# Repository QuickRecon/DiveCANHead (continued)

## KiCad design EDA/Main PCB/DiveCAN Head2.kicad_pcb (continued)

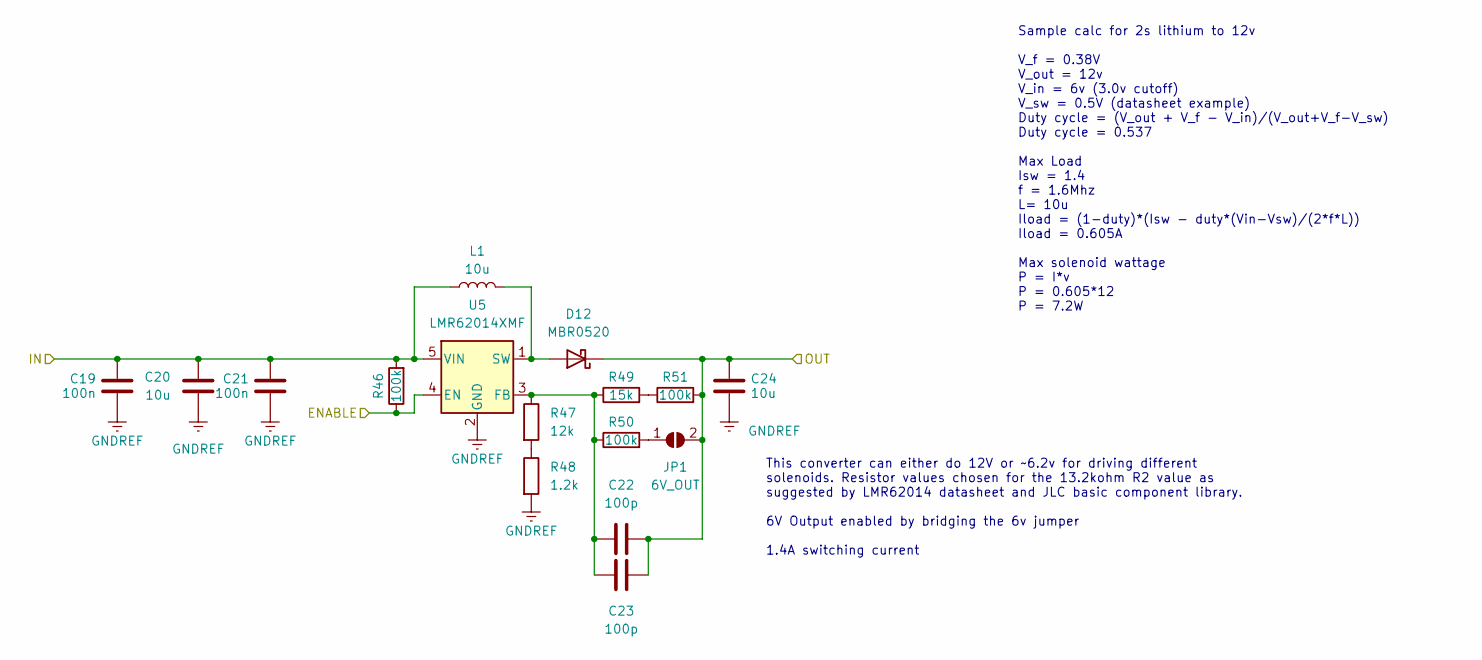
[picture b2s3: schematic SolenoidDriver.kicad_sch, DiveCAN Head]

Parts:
C19, C21: 100n; C_0603_1608Metric; MPN C14663
C20, C24: 10u; C_0603_1608Metric; MPN C96446
C22, C23: 100p; C_0402_1005Metric; MPN C1546
D12: MBR0520; D_SOD-123; MPN C5204745
JP1: 6V_OUT; SolderJumper-2_P1.3mm_Open_TrianglePad1.0x1.5mm
L1: 10u; L_SunItech_SLO0530H; MPN C325966
R46, R50, R51: 100k; R_0402_1005Metric; MPN C25741
R47: 12k; R_0402_1005Metric; MPN C25752
R48: 1.2k; R_0402_1005Metric; MPN C25862
R49: 15k; R_0402_1005Metric; MPN C25756
U5: LMR62014XMF; SOT-23-5; MPN C468235

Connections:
/Power Distribution/SOLENOID_PWR: C19.2, C20.1, C21.2, L1.1, R46.2, U5.5 (VIN); also elsewhere on the board
/SOLENOID: R46.1, U5.4 (EN); also elsewhere on the board
/SOL_OUT: C22.1, C23.1, C24.1, D12.1 (K), JP1.2 (B), R51.2; also elsewhere on the board
GNDREF: C19.1, C20.2, C21.1, C24.2, R48.2, U5.2 (GND); also elsewhere on the board
unnamed: D12.2 (A), L1.2, U5.1 (SW)
unnamed: JP1.1 (A), R50.2
unnamed: R47.2, R48.1
unnamed: R49.2, R51.1
unnamed: C22.2, C23.2, R47.1, R49.1, R50.1, U5.3 (FB)

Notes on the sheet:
Sample calc for 2s lithium to 12v V_f = 0.38V V_out = 12v V_in = 6v (3.0v cutoff) V_sw = 0.5V (datasheet example) Duty cycle = (V_out + V_f - V_in)/(V_out+V_f-V_sw) Duty cycle = 0.537 Max Load Isw = 1.4 f = 1.6Mhz L= 10u Iload = (1-duty)*(Isw - duty*(Vin-Vsw)/(2*f*L)) Iload = 0.605A Max solenoid wa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
This converter can either do 12V or ~6.2v for driving different solenoids. Resistor values chosen for the 13.2kohm R2 value as suggested by LMR62014 datasheet and JLC basic component library. 6V Output enabled by bridging the 6v jumper 1.4A switching current

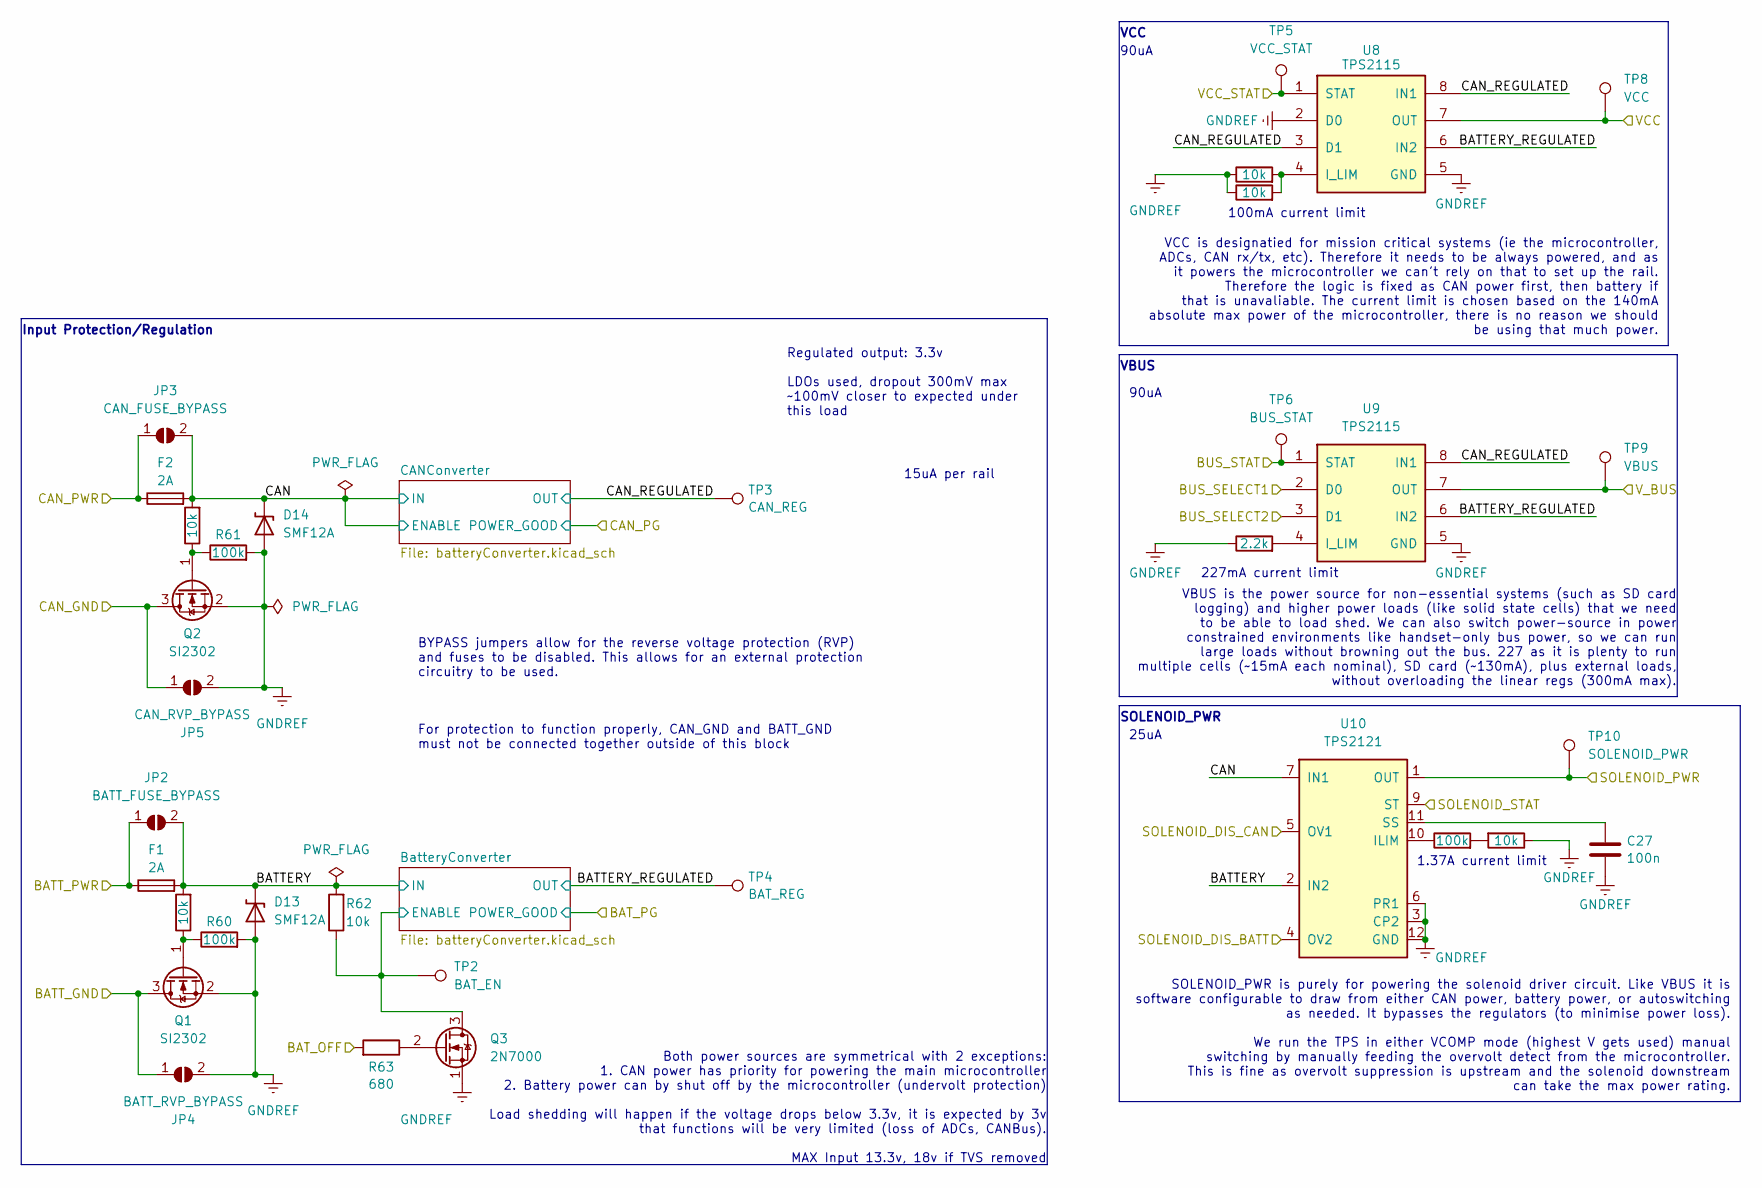
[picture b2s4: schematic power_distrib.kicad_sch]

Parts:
C27: 100n; C_0603_1608Metric; MPN C14663
D13, D14: SMF12A; D_SOD-123F; MPN C178259
F1, F2: 2A; Fuseholder_Littelfuse_Nano2_154x; MPN C108518
JP2: BATT_FUSE_BYPASS; SolderJumper-2_P1.3mm_Open_TrianglePad1.0x1.5mm
JP3: CAN_FUSE_BYPASS; SolderJumper-2_P1.3mm_Open_TrianglePad1.0x1.5mm
JP4: BATT_RVP_BYPASS; SolderJumper-2_P1.3mm_Open_TrianglePad1.0x1.5mm
JP5: CAN_RVP_BYPASS; SolderJumper-2_P1.3mm_Open_TrianglePad1.0x1.5mm
Q1, Q2: SI2302; SOT-23; MPN C181087; JlcRotOffset 180
Q3: 2N7000; SOT-23; MPN C8545; JlcRotOffset 180
R58, R59, R62, R65, R66, R70: 10k; R_0402_1005Metric; MPN C25744
R60, R61, R69: 100k; R_0402_1005Metric; MPN C25741
R63: 680; R_0402_1005Metric; MPN C25130
R67: 2.2k; R_0402_1005Metric; MPN C25879
TP2: BAT_EN; TestPoint_THTPad_D1.0mm_Drill0.5mm
TP3: CAN_REG; TestPoint_THTPad_D1.0mm_Drill0.5mm
TP4: BAT_REG; TestPoint_THTPad_D1.0mm_Drill0.5mm
TP5: VCC_STAT; TestPoint_THTPad_D1.0mm_Drill0.5mm
TP6: BUS_STAT; TestPoint_THTPad_D1.0mm_Drill0.5mm
TP8: VCC; TestPoint_THTPad_D1.0mm_Drill0.5mm
TP9: VBUS; TestPoint_THTPad_D1.0mm_Drill0.5mm
TP10: SOLENOID_PWR; TestPoint_THTPad_D1.0mm_Drill0.5mm
U8, U9: TPS2115; VSON-8_3.3x3.3mm_P0.65mm_NexFET; MPN C140321; JLCPCB Rotation Offset 90
U10: TPS2121; Texas_VQFN-HR-12_2x2.5mm_P0.5mm; JLC Part # C485916

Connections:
/BATTERY: F1.1, JP2.1 (A); also elsewhere on the board
/BATT_OFF: R63.2; also elsewhere on the board
/BUS_SEL1: U9.2 (D0); also elsewhere on the board
/BUS_SEL2: U9.3 (D1); also elsewhere on the board
/BUS_STAT: TP6.1, U9.1 (STAT); also elsewhere on the board
/CAN_GND: JP5.1 (A), Q2.3 (D); also elsewhere on the board
/CAN_PWR: F2.1, JP3.1 (A); also elsewhere on the board
/Power Distribution/BATTERY: D13.1 (A1), F1.2, JP2.2 (B), R58.2, R62.2, U10.2 (IN2); also elsewhere on the board
/Power Distribution/BATTERY_REGULATED: TP4.1, U8.6 (IN2), U9.6 (IN2); also elsewhere on the board
/Power Distribution/BATT_GND: JP4.1 (A), Q1.3 (D); also elsewhere on the board
/Power Distribution/BatteryConverter/ENABLE: Q3.3 (D), R62.1, TP2.1; also elsewhere on the board
/Power Distribution/CAN: D14.1 (A1), F2.2, JP3.2 (B), R59.2, U10.7 (IN1); also elsewhere on the board
/Power Distribution/CAN_REGULATED: TP3.1, U8.3 (D1), U8.8 (IN1), U9.8 (IN1); also elsewhere on the board
/Power Distribution/SOLENOID_PWR: TP10.1, U10.1 (OUT), U10.8 (OUT); also elsewhere on the board
/SOL_DIS_BATT: U10.4 (OV2); also elsewhere on the board
/SOL_DIS_CAN: U10.5 (OV1); also elsewhere on the board
/SOL_STAT: U10.9 (ST); also elsewhere on the board
/VCC_STAT: TP5.1, U8.1 (STAT); also elsewhere on the board
GNDREF: C27.2, D13.2 (A2), D14.2 (A2), JP4.2 (B), JP5.2 (B), Q1.2 (S), Q2.2 (S), Q3.1 (S), R60.2, R61.2, R65.1, R66.1, R67.1, R70.1, U8.2 (D0), U8.5 (GND), U9.5 (GND), U10.3 (CP2), U10.6 (PR1), U10.12 (GND); also elsewhere on the board
unnamed: Q1.1 (G), R58.1, R60.1
unnamed: Q2.1 (G), R59.1, R61.1
unnamed: Q3.2 (G), R63.1
unnamed: R69.2, R70.2
unnamed: R65.2, R66.2, U8.4 (I_LIM)
unnamed: R67.2, U9.4 (I_LIM)
unnamed: R69.1, U10.10 (ILIM)
unnamed: C27.1, U10.11 (SS)
VBUS: TP9.1, U9.7 (OUT); also elsewhere on the board
VCC: TP8.1, U8.7 (OUT); also elsewhere on the board

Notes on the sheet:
Both power sources are symmetrical with 2 exceptions: 1. CAN power has priority for powering the main microcontroller 2. Battery power can by shut off by the microcontroller (undervolt protection) Load shedding will happen if the voltage drops below 3.3v, it is expected by 3v that functions will be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
SOLENOID_PWR
25uA
VBUS is the power source for non-essential systems (such as SD card logging) and higher power loads (like solid state cells) that we need to be able to load shed. We can also switch power-source in power constrained environments like handset-only bus power, so we can run large loads without brownin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
15uA per rail
100mA current limit
90uA
Input Protection/Regulation
227mA current limit
VCC is designatied for mission critical systems (ie the microcontroller, ADCs, CAN rx/tx, etc). Therefore it needs to be always powered, and as it powers the microcontroller we can't rely on that to set up the rail. Therefore the logic is fixed as CAN power first, then battery if that is unavaliabl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
VCC
Regulated output: 3.3v LDOs used, dropout 300mV max ~100mV closer to expected under this load
VBUS
For protection to function properly, CAN_GND and BATT_GND must not be connected together outside of this block
1.37A current limit
BYPASS jumpers allow for the reverse voltage protection (RVP) and fuses to be disabled. This allows for an external protection circuitry to be used.
SOLENOID_PWR is purely for powering the solenoid driver circuit. Like VBUS it is software configurable to draw from either CAN power, battery power, or autoswitching as needed. It bypasses the regulators (to minimise power loss). We run the TPS in either VCOMP mode (highest V gets used) manual swit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

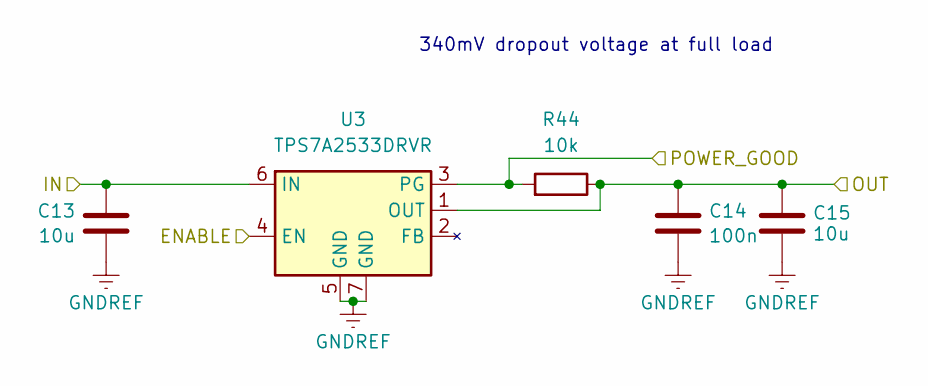
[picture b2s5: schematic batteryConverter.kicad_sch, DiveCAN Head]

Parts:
C13, C15: 10u; C_0603_1608Metric; MPN C96446
C14: 100n; C_0603_1608Metric; MPN C14663
R44: 10k; R_0402_1005Metric; MPN C25744
U3: TPS7A2533DRVR; WSON-6-1EP_2x2mm_P0.65mm_EP1x1.6mm_ThermalVias; MPN C2867820; JlcRotOffset 0

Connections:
/Power Distribution/CAN: C13.1, U3.4 (EN), U3.6 (IN); also elsewhere on the board
/Power Distribution/CAN_PG: R44.2, U3.3 (PG)
/Power Distribution/CAN_REGULATED: C14.1, C15.1, R44.1, U3.1 (OUT); also elsewhere on the board
GNDREF: C13.2, C14.2, C15.2, U3.5 (GND), U3.7 (GND); also elsewhere on the board

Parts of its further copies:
C16, C18: 10u; C_0603_1608Metric; MPN C96446
C17: 100n; C_0603_1608Metric; MPN C14663
R45: 10k; R_0402_1005Metric; MPN C25744
U4: TPS7A2533DRVR; WSON-6-1EP_2x2mm_P0.65mm_EP1x1.6mm_ThermalVias; MPN C2867820; JlcRotOffset 0

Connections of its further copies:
/Power Distribution/BATTERY: C16.1, U4.6 (IN); also elsewhere on the board
/Power Distribution/BATTERY_REGULATED: C17.1, C18.1, R45.1, U4.1 (OUT); also elsewhere on the board
/Power Distribution/BAT_PG: R45.2, U4.3 (PG)
/Power Distribution/BatteryConverter/ENABLE: U4.4 (EN); also elsewhere on the board
GNDREF: C16.2, C17.2, C18.2, U4.5 (GND), U4.7 (GND); also elsewhere on the board

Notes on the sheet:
340mV dropout voltage at full load

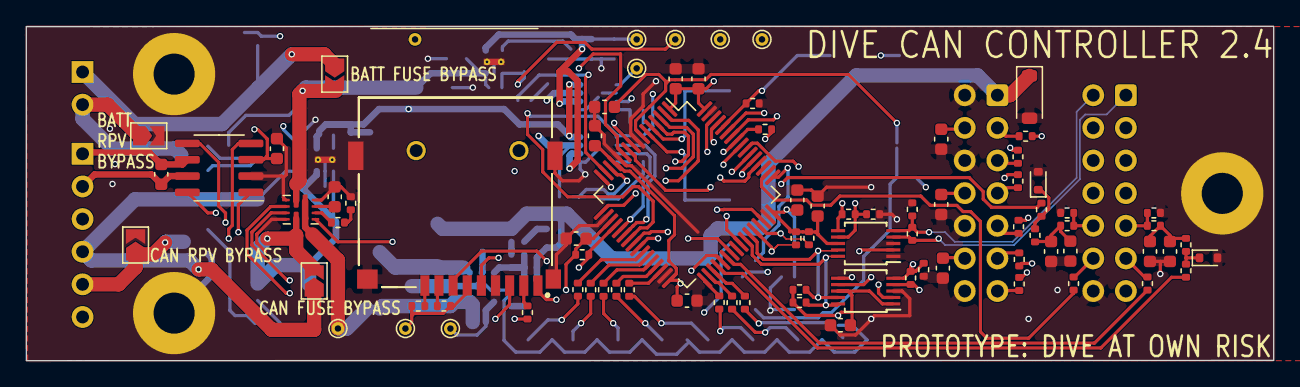
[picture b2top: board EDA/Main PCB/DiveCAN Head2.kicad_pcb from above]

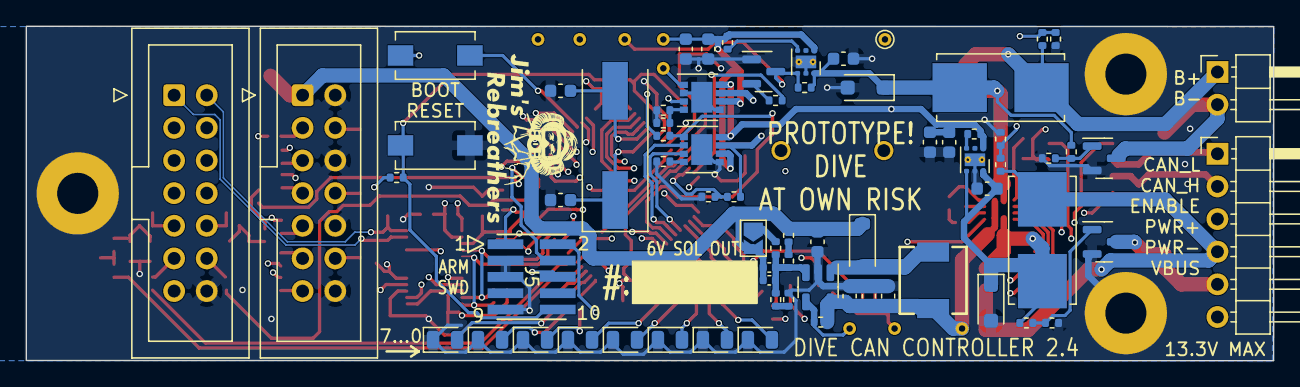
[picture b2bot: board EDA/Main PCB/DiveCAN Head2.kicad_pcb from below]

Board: 4 copper layers, 97.1 x 26.0 mm, 156 parts (71 on the bottom side), 114 nets.

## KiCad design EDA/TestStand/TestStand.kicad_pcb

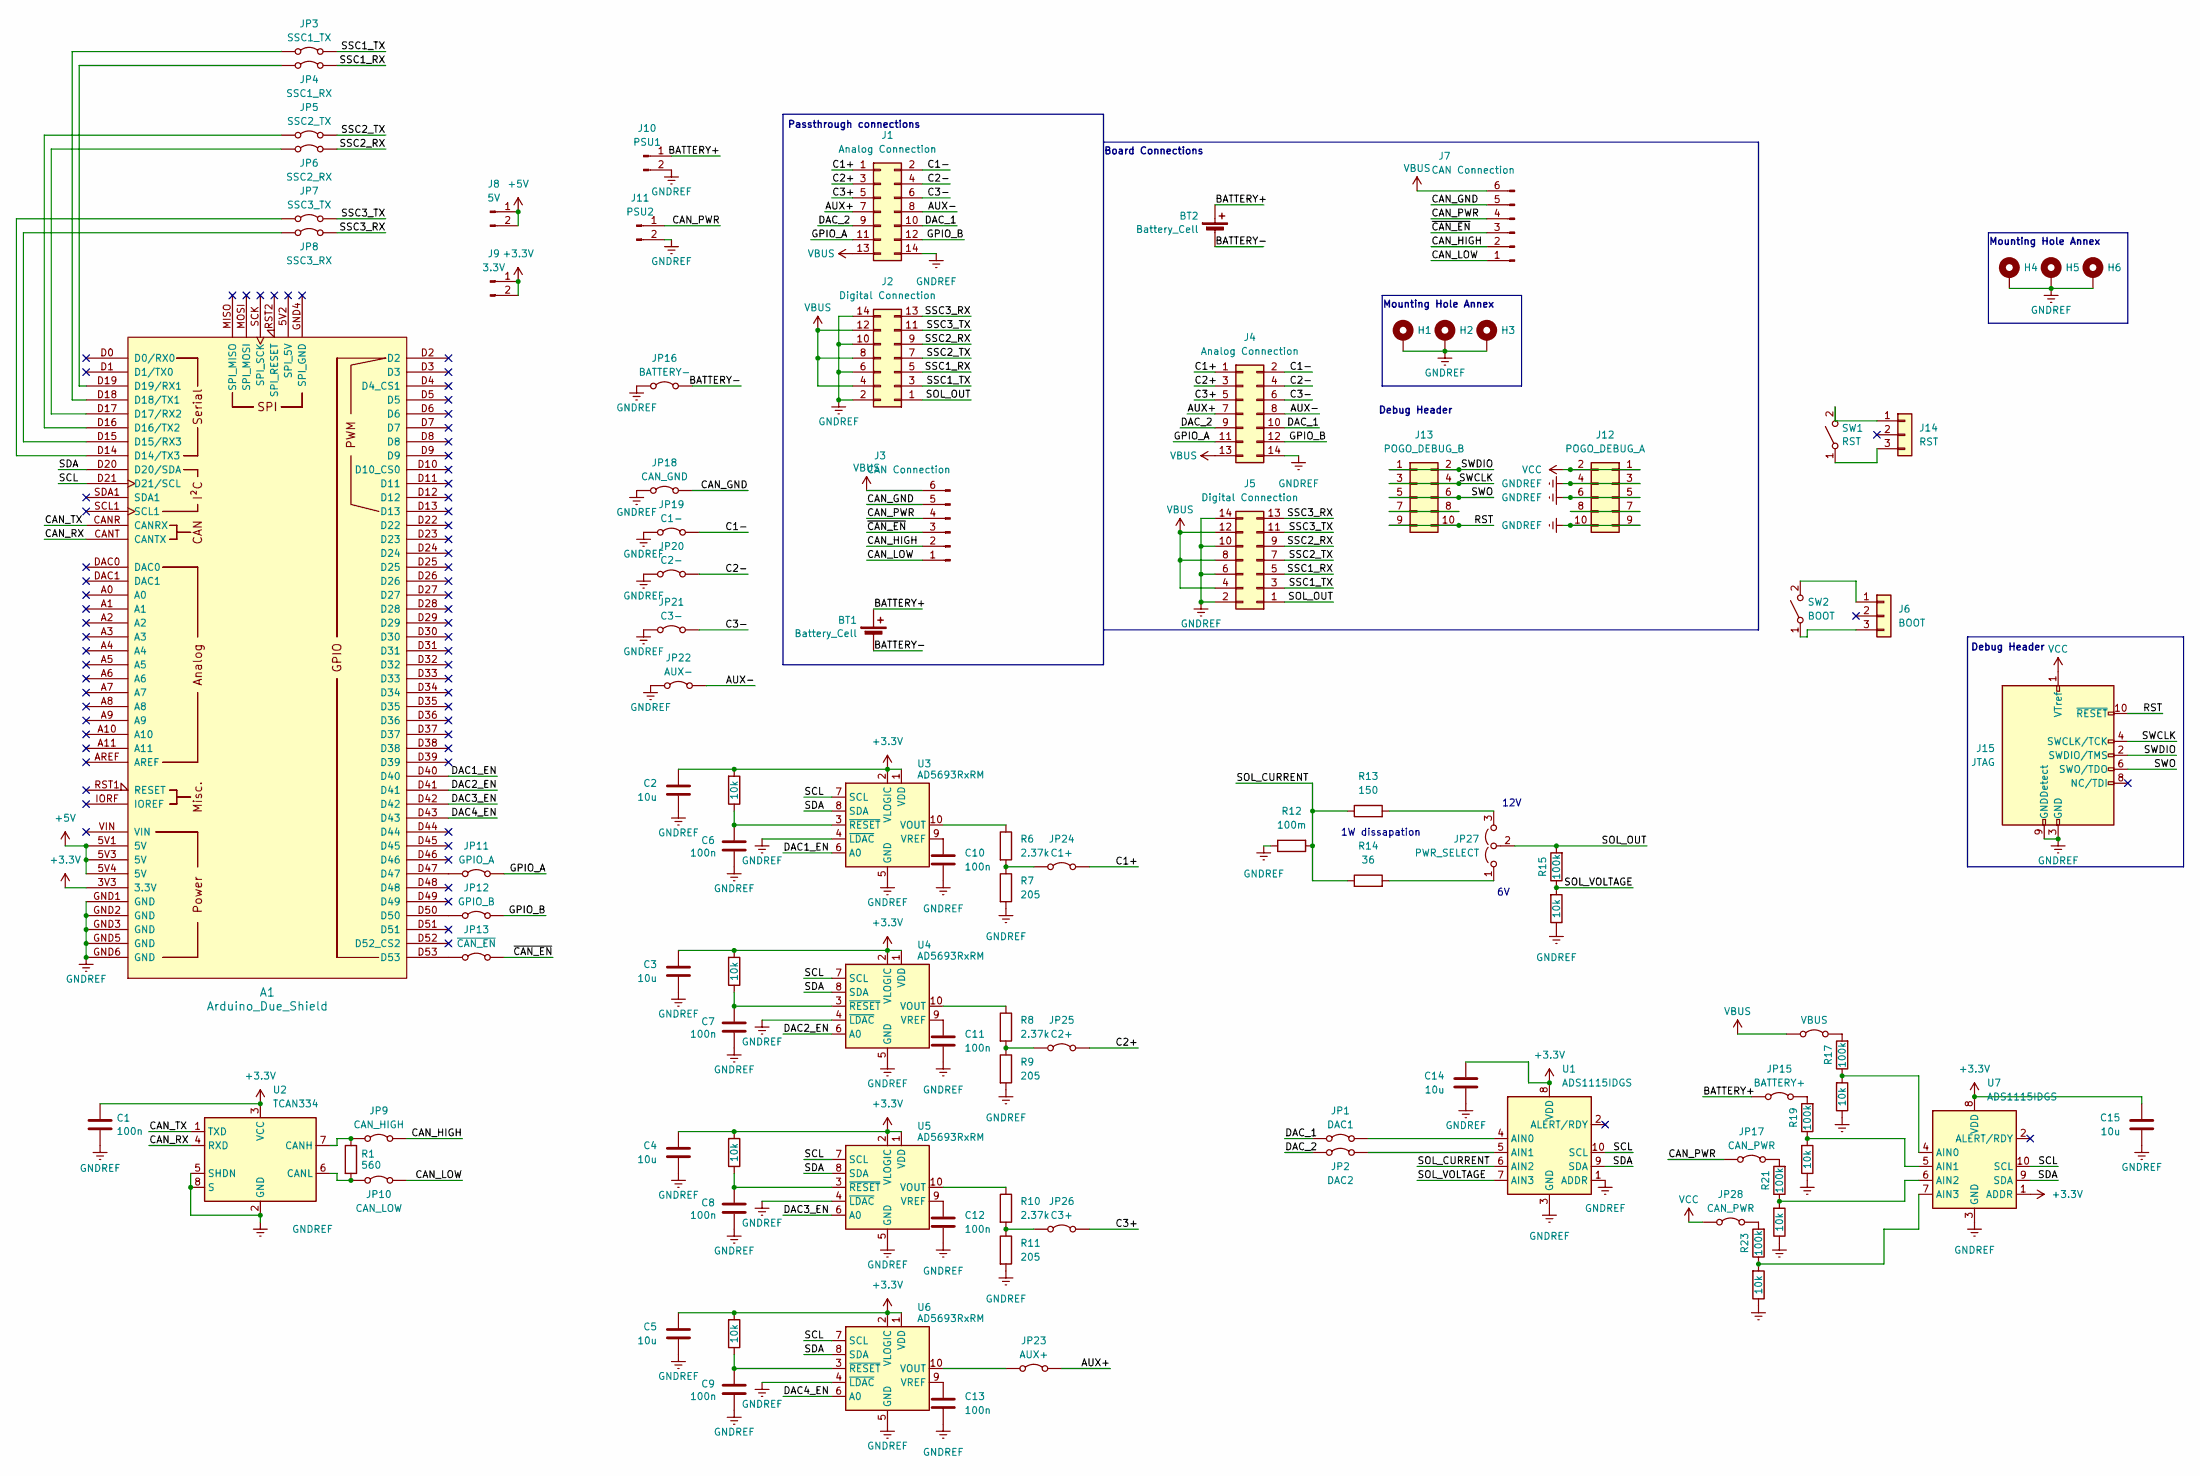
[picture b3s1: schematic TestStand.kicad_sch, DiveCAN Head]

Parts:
A1: Arduino_Due_Shield
BT1, BT2: Battery_Cell; PinHeader_1x02_P2.54mm_Horizontal
C1, C6, C7, C8, C9, C10, C11, C12, C13: 100n; C_0603_1608Metric; MPN C14663
C2, C3, C4, C5, C14, C15: 10u; C_0603_1608Metric; MPN C96446
H1, H2, H3, H4, H5, H6: MountingHole_Pad; MountingHole_3.2mm_M3_Pad
J1, J4: Analog Connection; IDC-Header_2x07_P2.54mm_Vertical
J2, J5: Digital Connection; IDC-Header_2x07_P2.54mm_Vertical
J3, J7: CAN Connection; PinHeader_1x06_P2.54mm_Horizontal
J6: BOOT; PinHeader_1x03_P2.54mm_Vertical
J8: 5V; PinHeader_1x02_P2.54mm_Vertical
J9: 3.3V; PinHeader_1x02_P2.54mm_Vertical
J10: PSU1; PinHeader_1x02_P2.54mm_Horizontal
J11: PSU2; PinHeader_1x02_P2.54mm_Horizontal
J12: POGO_DEBUG_A; PinHeader_2x05_P1.27mm_Vertical
J13: POGO_DEBUG_B; PinHeader_2x05_P1.27mm_Vertical
J14: RST; PinHeader_1x03_P2.54mm_Vertical
J15: JTAG; CON10_2X5_DUK_FTSH_SAI; MPN C448647
JP1: DAC1; PinHeader_1x02_P2.54mm_Vertical
JP2: DAC2; PinHeader_1x02_P2.54mm_Vertical
JP3: SSC1_TX; PinHeader_1x02_P2.54mm_Vertical
JP4: SSC1_RX; PinHeader_1x02_P2.54mm_Vertical
JP5: SSC2_TX; PinHeader_1x02_P2.54mm_Vertical
JP6: SSC2_RX; PinHeader_1x02_P2.54mm_Vertical
JP7: SSC3_TX; PinHeader_1x02_P2.54mm_Vertical
JP8: SSC3_RX; PinHeader_1x02_P2.54mm_Vertical
JP9: CAN_HIGH; PinHeader_1x02_P2.54mm_Vertical
JP10: CAN_LOW; PinHeader_1x02_P2.54mm_Vertical
JP11: GPIO_A; PinHeader_1x02_P2.54mm_Vertical
JP12: GPIO_B; PinHeader_1x02_P2.54mm_Vertical
JP13: ~{CAN_EN}; PinHeader_1x02_P2.54mm_Vertical
JP14: VBUS; PinHeader_1x02_P2.54mm_Vertical
JP15: BATTERY+; PinHeader_1x02_P2.54mm_Vertical
JP16: BATTERY-; PinHeader_1x02_P2.54mm_Vertical
JP17, JP28: CAN_PWR; PinHeader_1x02_P2.54mm_Vertical
JP18: CAN_GND; PinHeader_1x02_P2.54mm_Vertical
JP19: C1-; PinHeader_1x02_P2.54mm_Vertical
JP20: C2-; PinHeader_1x02_P2.54mm_Vertical
JP21: C3-; PinHeader_1x02_P2.54mm_Vertical
JP22: AUX-; PinHeader_1x02_P2.54mm_Vertical
JP23: AUX+; PinHeader_1x02_P2.54mm_Vertical
JP24: C1+; PinHeader_1x02_P2.54mm_Vertical
JP25: C2+; PinHeader_1x02_P2.54mm_Vertical
JP26: C3+; PinHeader_1x02_P2.54mm_Vertical
JP27: PWR_SELECT; PinHeader_1x03_P2.54mm_Vertical
R1: 560; R_0402_1005Metric; MPN C163460
R2, R3, R4, R5, R16, R18, R20, R22, R24: 10k; R_0402_1005Metric; MPN C25744
R6, R8, R10: 2.37k; R_0402_1005Metric; MPN C517661
R7, R9, R11: 205; R_0402_1005Metric; MPN C517799
R12: 100m; R_2512_6332Metric; MPN C160587
R13: 150; R_Axial_DIN0922_L20.0mm_D9.0mm_P25.40mm_Horizontal
R14: 36; R_Axial_DIN0922_L20.0mm_D9.0mm_P25.40mm_Horizontal
R15, R17, R19, R21, R23: 100k; R_0402_1005Metric; MPN C25741
SW1: RST; SW_SPST_EVQPE1; MPN C2915176
SW2: BOOT; SW_SPST_EVQPE1; MPN C2915176
U1, U7: ADS1115IDGS; TSSOP-10_3x3mm_P0.5mm
U2: TCAN334; SOIC-8_3.9x4.9mm_P1.27mm; MPN C2871143; JlcRotOffset -90
U3, U4, U5, U6: AD5693RxRM; MSOP-10_3x3mm_P0.5mm; MPN C650136

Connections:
+3.3V: A1.3V3 (3.3V), C1.1, C2.1, C3.1, C4.1, C5.1, C14.1, C15.1, J9.1, J9.2, R2.2, R3.2, R4.2, R5.2, U1.8 (VDD), U2.3 (VCC), U3.1 (VDD), U3.2 (VLOGIC), U4.1 (VDD), U4.2 (VLOGIC), U5.1 (VDD), U5.2 (VLOGIC), U6.1 (VDD), U6.2 (VLOGIC), U7.1 (ADDR), U7.8 (VDD)
+5V: A1.5V1 (5V), A1.5V3 (5V), A1.5V4 (5V), J8.1, J8.2
/AUX+: J1.7, J4.7, JP23.2 (B)
/AUX-: J1.8, J4.8, JP22.2 (B)
/BATTERY+: BT1.1 (+), BT2.1 (+), J10.1, JP15.2 (B)
/BATTERY-: BT1.2 (-), BT2.2 (-), JP16.2 (B)
/C1+: J1.1, J4.1, JP24.2 (B)
/C1-: J1.2, J4.2, JP19.2 (B)
/C2+: J1.3, J4.3, JP25.2 (B)
/C2-: J1.4, J4.4, JP20.2 (B)
/C3+: J1.5, J4.5, JP26.2 (B)
/C3-: J1.6, J4.6, JP21.2 (B)
/CAN_GND: J3.5, J7.5, JP18.2 (B)
/CAN_HIGH: J3.2, J7.2, JP9.2 (B)
/CAN_LOW: J3.1, J7.1, JP10.2 (B)
/CAN_PWR: J3.4, J7.4, J11.1, JP17.2 (B)
/CAN_RX: A1.CANT (CANTX), U2.4 (RXD)
/CAN_TX: A1.CANR (CANRX), U2.1 (TXD)
/DAC1_EN: A1.D40, U3.6 (A0)
/DAC2_EN: A1.D41, U4.6 (A0)
/DAC3_EN: A1.D42, U5.6 (A0)
/DAC4_EN: A1.D43, U6.6 (A0)
/DAC_1: J1.10, J4.10, JP1.1 (A)
/DAC_2: J1.9, J4.9, JP2.1 (A)
/GPIO_A: J1.11, J4.11, JP11.2 (B)
/GPIO_B: J1.12, J4.12, JP12.2 (B)
/RST: J13.9, J13.10, J15.10 (~RESET)
/SCL: A1.D21 (D21/SCL), U1.10 (SCL), U3.7 (SCL), U4.7 (SCL), U5.7 (SCL), U6.7 (SCL), U7.10 (SCL)
/SDA: A1.D20 (D20/SDA), U1.9 (SDA), U3.8 (SDA), U4.8 (SDA), U5.8 (SDA), U6.8 (SDA), U7.9 (SDA)
/SOL_CURRENT: R12.2, R13.1, R14.1, U1.6 (AIN2)
/SOL_OUT: J2.1, J5.1, JP27.2 (C), R15.2
/SOL_VOLTAGE: R15.1, R16.2, U1.7 (AIN3)
/SSC1_RX: J2.5, J5.5, JP4.2 (B)
/SSC1_TX: J2.3, J5.3, JP3.2 (B)
/SSC2_RX: J2.9, J5.9, JP6.2 (B)
/SSC2_TX: J2.7, J5.7, JP5.2 (B)
/SSC3_RX: J2.13, J5.13, JP8.2 (B)
/SSC3_TX: J2.11, J5.11, JP7.2 (B)
/SWCLK: J13.3, J13.4, J15.4 (SWCLK/TCK)
/SWDIO: J13.1, J13.2, J15.2 (SWDIO/TMS)
/SWO: J13.5, J13.6, J15.6 (SWO/TDO)
/~CAN_EN: J3.3, J7.3, JP13.2 (B)
GNDREF: A1.GND1 (GND), A1.GND2 (GND), A1.GND3 (GND), A1.GND5 (GND), A1.GND6 (GND), C1.2, C2.2, C3.2, C4.2, C5.2, C6.2, C7.2, C8.2, C9.2, C10.2, C11.2, C12.2, C13.2, C14.2, C15.2, H1.1, H2.1, H3.1, H4.1, H5.1, H6.1, J1.14, J2.2, J2.6, J2.10, J2.14, J4.14, J5.2, J5.6, J5.10, J5.14, J10.2, J11.2, J12.3, J12.4, J12.5, J12.6, J12.9, J12.10, J15.3 (GND), J15.5 (GND), J15.9 (GNDDetect), JP16.1 (A), JP18.1 (A), JP19.1 (A), JP20.1 (A), JP21.1 (A), JP22.1 (A), R7.2, R9.2, R11.2, R12.1, R16.1, R18.1, R20.1, R22.1, R24.1, U1.1 (ADDR), U1.3 (GND), U2.2 (GND), U2.5 (SHDN), U2.8 (S), U3.4 (~LDAC), U3.5 (GND), U4.4 (~LDAC), U4.5 (GND), U5.4 (~LDAC), U5.5 (GND), U6.4 (~LDAC), U6.5 (GND), U7.3 (GND)
unnamed: A1.D14 (D14/TX3), JP7.1 (A)
unnamed: A1.D15 (D15/RX3), JP8.1 (A)
unnamed: A1.D16 (D16/TX2), JP5.1 (A)
unnamed: A1.D17 (D17/RX2), JP6.1 (A)
unnamed: A1.D18 (D18/TX1), JP3.1 (A)
unnamed: A1.D19 (D19/RX1), JP4.1 (A)
unnamed: J6.1, SW2.2 (B)
unnamed: J6.3, SW2.1 (A)
unnamed: J12.7, J12.8
unnamed: J13.7, J13.8
unnamed: J14.1, SW1.2 (B)
unnamed: J14.3, SW1.1 (A)
unnamed: JP1.2 (B), U1.4 (AIN0)
unnamed: JP2.2 (B), U1.5 (AIN1)
unnamed: JP9.1 (A), R1.1, U2.7 (CANH)
unnamed: JP10.1 (A), R1.2, U2.6 (CANL)
unnamed: A1.D47, JP11.1 (A)
unnamed: A1.D50, JP12.1 (A)
unnamed: A1.D53, JP13.1 (A)
unnamed: JP14.1 (A), R17.2
unnamed: JP15.1 (A), R19.2
unnamed: JP17.1 (A), R21.2
unnamed: JP23.1 (A), U6.10 (VOUT)
unnamed: JP24.1 (A), R6.2, R7.1
unnamed: JP25.1 (A), R8.2, R9.1
unnamed: JP26.1 (A), R10.2, R11.1
unnamed: JP27.1 (A), R14.2
unnamed: JP27.3 (B), R13.2
unnamed: JP28.1 (A), R23.2
unnamed: R6.1, U3.10 (VOUT)
unnamed: C10.1, U3.9 (VREF)
unnamed: C6.1, R2.1, U3.3 (~RESET)
unnamed: R8.1, U4.10 (VOUT)
unnamed: C11.1, U4.9 (VREF)
unnamed: C7.1, R3.1, U4.3 (~RESET)
unnamed: R10.1, U5.10 (VOUT)
unnamed: C12.1, U5.9 (VREF)
unnamed: C8.1, R4.1, U5.3 (~RESET)
unnamed: C13.1, U6.9 (VREF)
unnamed: C9.1, R5.1, U6.3 (~RESET)
unnamed: R17.1, R18.2, U7.4 (AIN0)
unnamed: R19.1, R20.2, U7.5 (AIN1)
unnamed: R21.1, R22.2, U7.6 (AIN2)
unnamed: R23.1, R24.2, U7.7 (AIN3)
VBUS: J1.13, J2.4, J2.8, J2.12, J3.6, J4.13, J5.4, J5.8, J5.12, J7.6, JP14.2 (B)
VCC: J12.1, J12.2, J15.1 (VTref), JP28.2 (B)

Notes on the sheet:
Debug Header
Mounting Hole Annex
12V
Board Connections
Passthrough connections
1W dissapation

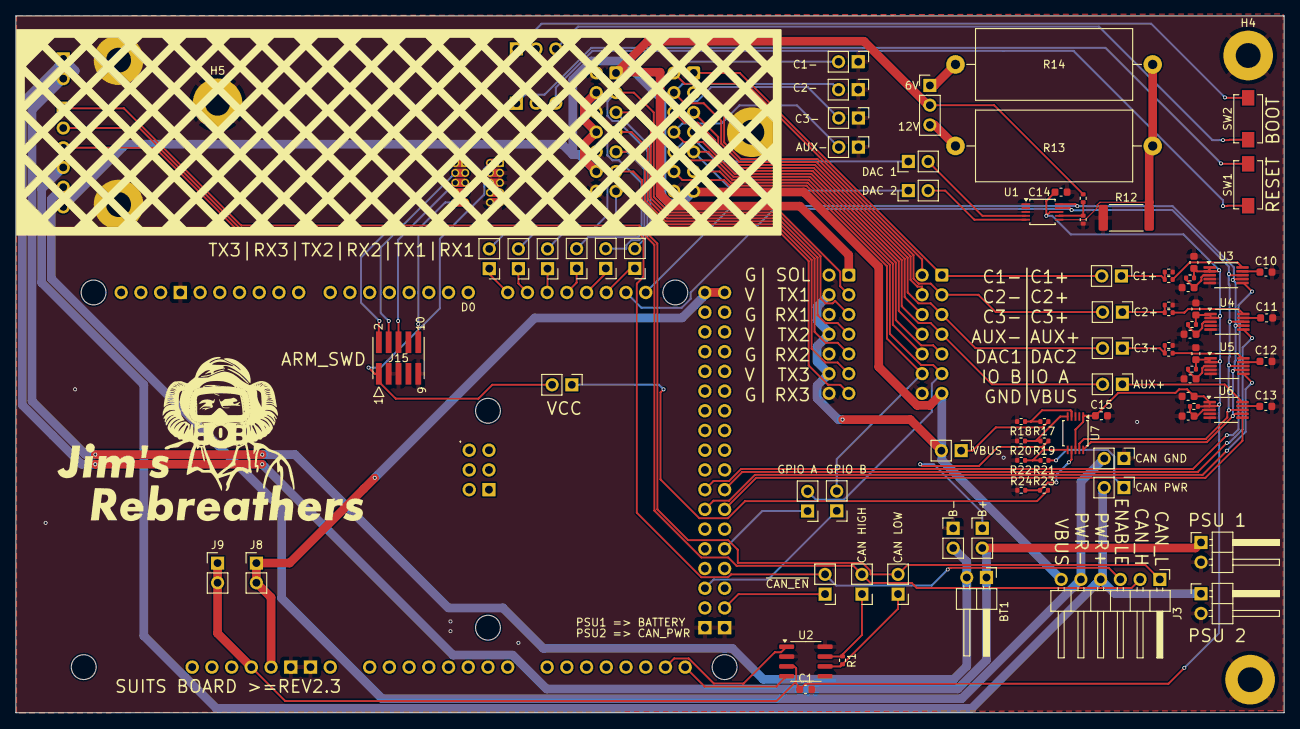
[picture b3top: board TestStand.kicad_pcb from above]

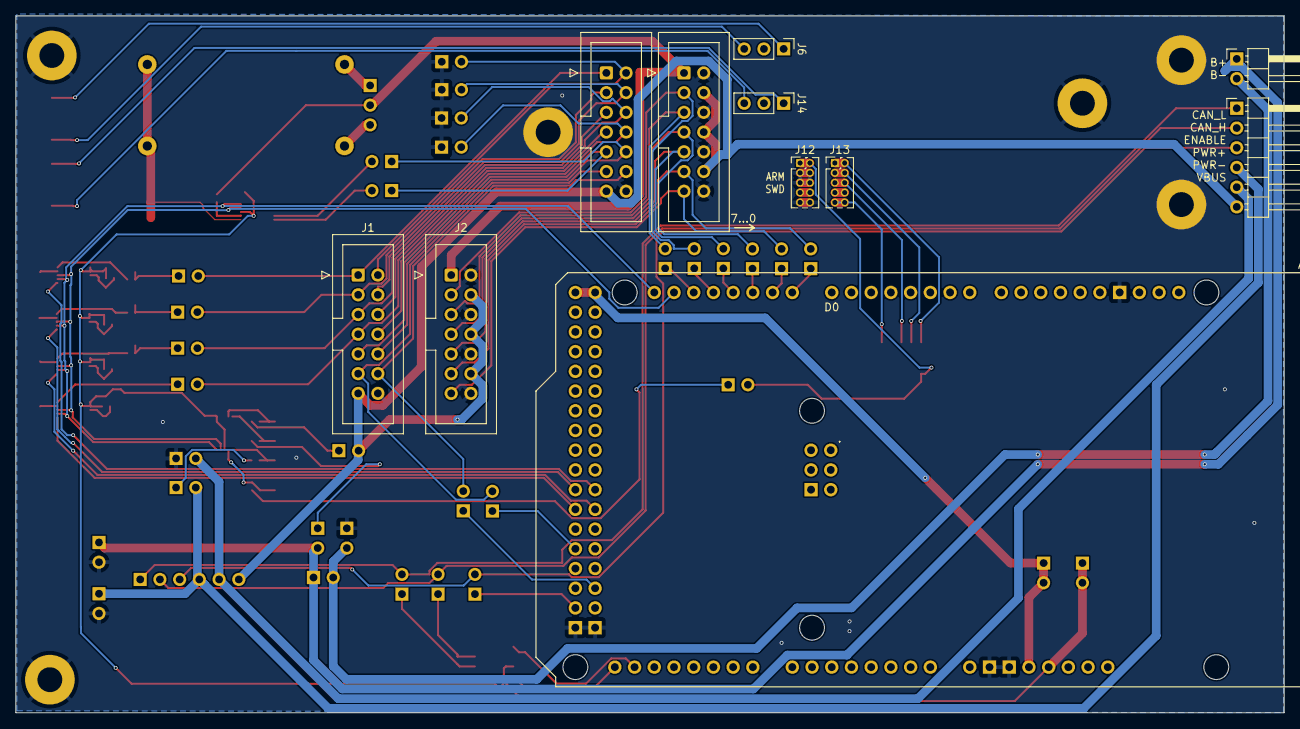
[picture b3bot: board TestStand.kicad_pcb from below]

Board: 2 copper layers, 163.3 x 89.8 mm, 100 parts (10 on the bottom side), 89 nets.
